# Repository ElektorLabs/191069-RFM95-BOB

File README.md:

# 191069-RFM95-BOB 

A BOB for the RFM95 LoRa module. Gerberfiles to be used with your preffered PCB service.
4x4 matrix version also included if you use a provider that has a fixed price for up to 100mmx100mm.
This will give you more BOB for your money.

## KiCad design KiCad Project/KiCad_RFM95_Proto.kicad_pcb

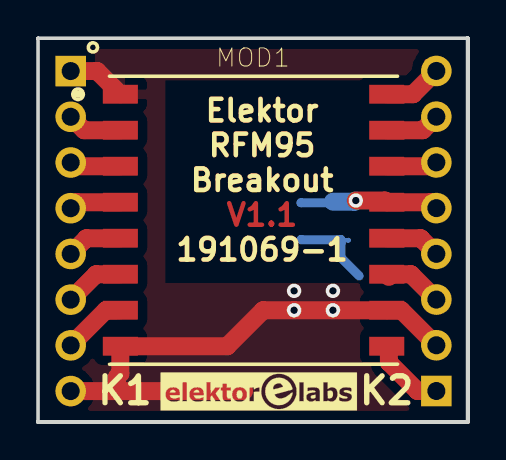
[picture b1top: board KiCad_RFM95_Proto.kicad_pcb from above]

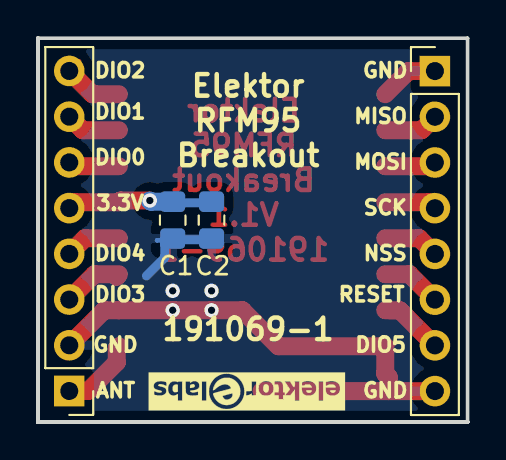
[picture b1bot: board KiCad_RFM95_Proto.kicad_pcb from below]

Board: 2 copper layers, 23.9 x 21.4 mm, 5 parts (4 on the bottom side), 14 nets.

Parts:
C1: 100nF / 10V; C_0805_2012Metric_Pad1.15x1.40mm_HandSolder
C2: 4.7µF / 10V; C_0805_2012Metric_Pad1.15x1.40mm_HandSolder
K1, K2: Conn_01x08_Male; PinHeader_1x08_P2.54mm_Vertical
MOD1: RFM95W-868S2; XCVR_RFM95W-868S2

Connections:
GND: C1.2, C2.2, K1.1, K1.8, K2.2, MOD1.1, MOD1.8, MOD1.10
unnamed: C1.1, C2.1, K2.5, MOD1.13
unnamed: K1.2, MOD1.2
unnamed: K1.3, MOD1.3
unnamed: K1.4, MOD1.4
unnamed: K1.5, MOD1.5
unnamed: K1.6, MOD1.6
unnamed: K1.7, MOD1.7
unnamed: K2.1, MOD1.9
unnamed: K2.3, MOD1.11
unnamed: K2.4, MOD1.12
unnamed: K2.6, MOD1.14
unnamed: K2.7, MOD1.15
unnamed: K2.8, MOD1.16

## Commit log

2021-03-04 first commit
    Gerberfiles only
2021-05-17 Added KiCad Project
    Added KiCad Project
